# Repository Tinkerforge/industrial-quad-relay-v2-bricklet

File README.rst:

Industrial Quad Relay Bricklet 2.0
==================================

This repository contains the firmware source code and the hardware design
files. The documentation generator configs can be found at
https://github.com/Tinkerforge/generators

Repository Content
------------------

software/:
 * examples/: Examples for all supported languages
 * build/: Compiled files
 * src/: Source code of firmware
 * Makefile: Makefile to build project

hardware/:
 * Contains KiCad project files and additionally schematics as PDF

datasheets/:
 * Contains datasheets for sensors and complex ICs that are used

Hardware
--------

The hardware is designed with the open source EDA Suite KiCad
(http://www.kicad.org). Before you are able to open the files,
you have to install the Tinkerforge kicad-libraries
(https://github.com/Tinkerforge/kicad-libraries). You can either clone
them directly in hardware/ or clone them in a separate folder and
symlink them into hardware/
(ln -s kicad_path/kicad-libraries project_path/hardware). After that you
can open the .pro file in hardware/ with KiCad and from there view and
modify the schematics and the PCB layout.

Software
--------

If you want to do your own Brick/Bricklet firmware development we highly
recommend that you use our build environment setup script and read the
tutorial (https://www.tinkerforge.com/en/doc/Tutorials/Tutorial_Build_Environment/Tutorial.html).

To compile the C code we recommend you to install the newest GNU Arm Embedded
Toolchain (https://launchpad.net/gcc-arm-embedded/+download).
You also need to install bricklib2 (https://github.com/Tinkerforge/bricklib2).

You can either clone it directly in software/src/ or clone it in a
separate folder and symlink it into software/src/
(ln -s bricklib_path/bricklib2 project_path/software/src/). Finally make sure to
have CMake installed (http://www.cmake.org/cmake/resources/software.html).

After that you can build the firmware by invoking make in software/.
The firmware (.zbin) can then be found in software/build/ and uploaded
with brickv (click button "Flashing" on start screen).

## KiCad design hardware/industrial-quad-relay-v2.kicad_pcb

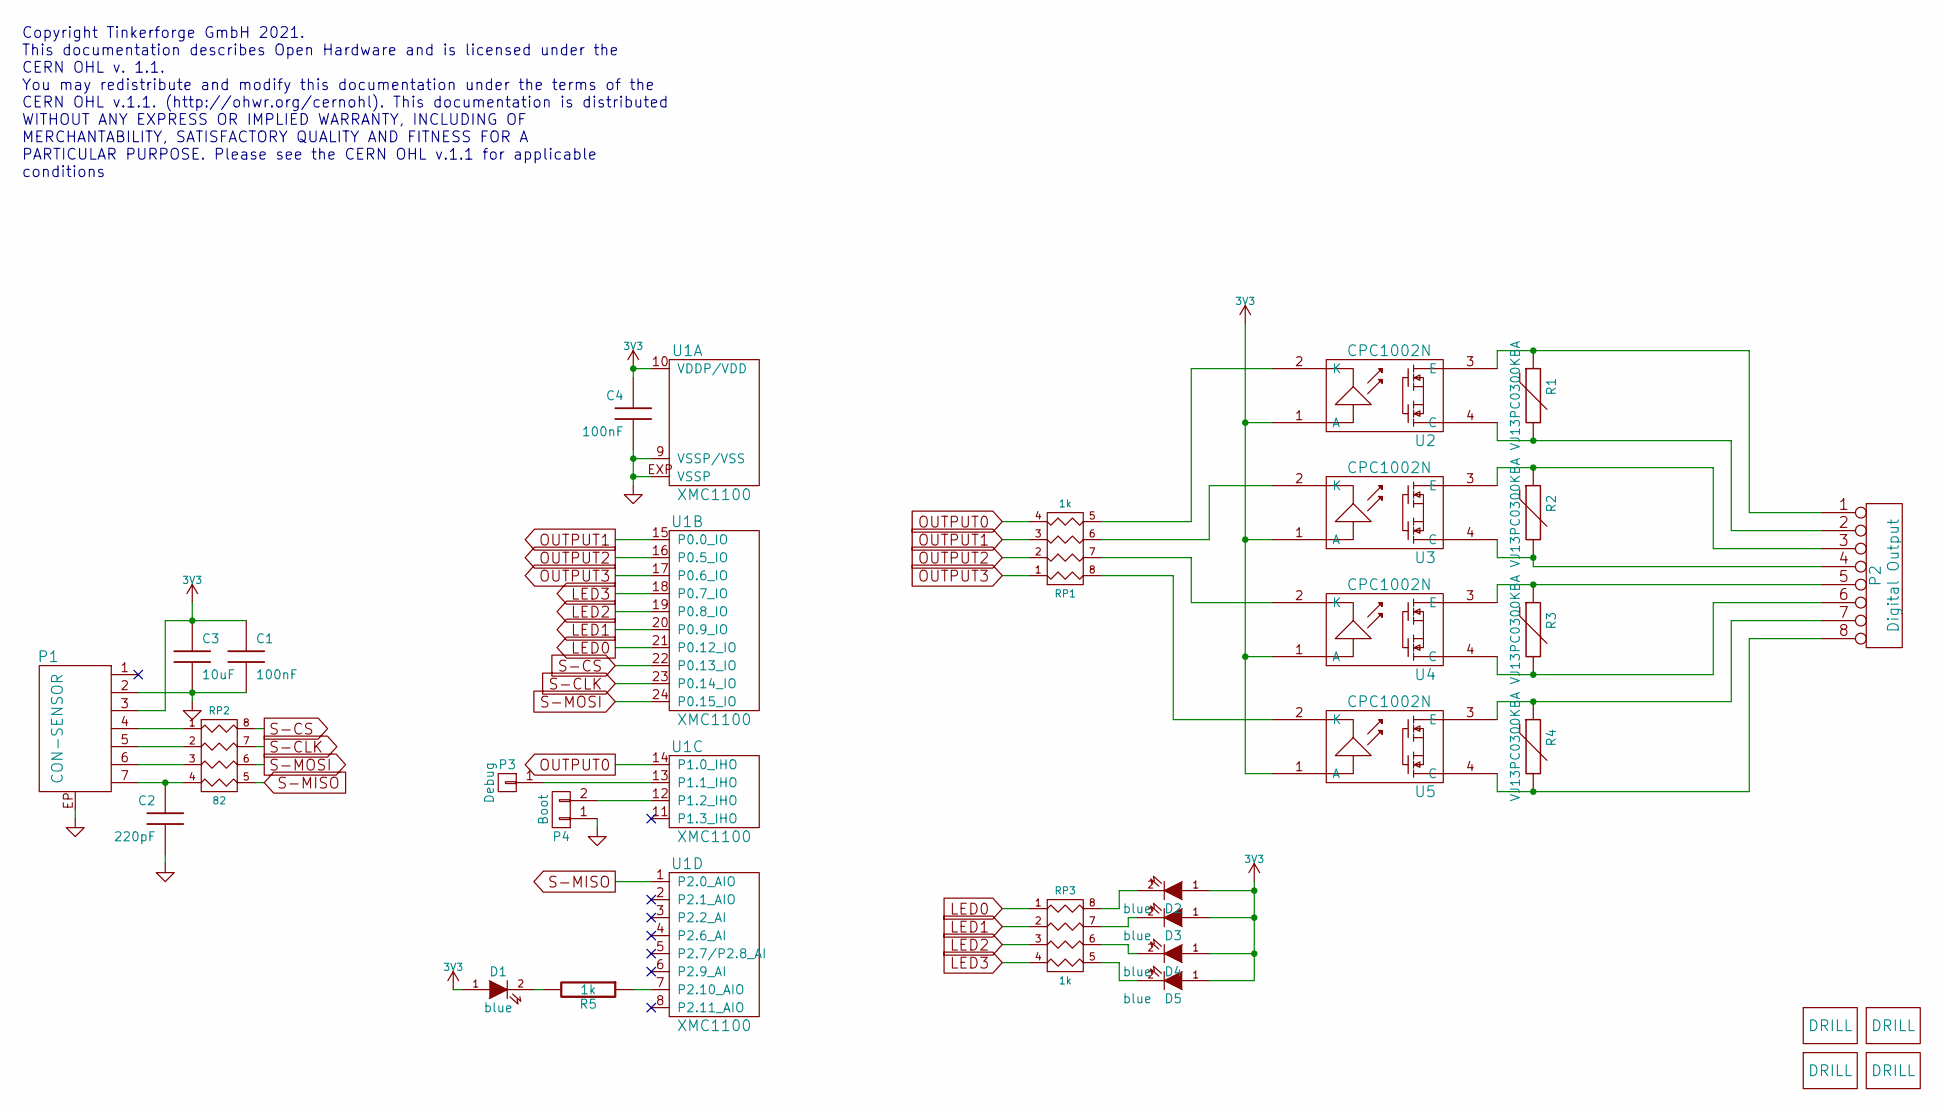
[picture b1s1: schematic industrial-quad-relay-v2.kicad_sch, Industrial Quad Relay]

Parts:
C1, C4: 100nF; C0603F
C2: 220pF; C0402F
C3: 10uF; C0805
D1, D2, D3, D4, D5: blue; D0603F
P1: CON-SENSOR; CON-SENSOR2
P2: Digital Output; OQ_8P
P3: Debug; DEBUG_PAD
P4: Boot; SolderJumper
R1, R2, R3, R4: VJ13PC0300KBA; R1210
R5: 1k; R0603F
RP1, RP3: 1k; 0603X4
RP2: 82; 4X0402
U1: XMC1100; QFN24-4x4mm-0.5mm
U2, U3, U4, U5: CPC1002N; SOP4-WIDE
U6, U7, U8, U9: DRILL; DRILL_NP

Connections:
3V3: C1.1, C3.1, C4.1, D1.1 (A), D2.1 (A), D3.1 (A), D4.1 (A), D5.1 (A), P1.3, U1.10 (VDDP/VDD), U2.1 (A), U3.1 (A), U4.1 (A), U5.1 (A)
GND: C1.2, C2.2, C3.2, C4.2, P1.2, P1.EP, P4.1, U1.9 (VSSP/VSS), U1.EXP (VSSP)
LED0: RP3.1, U1.21 (P0.12_IO)
LED1: RP3.2, U1.20 (P0.9_IO)
LED2: RP3.3, U1.19 (P0.8_IO)
LED3: RP3.4, U1.18 (P0.7_IO)
unnamed: C2.1, P1.7, RP2.4
unnamed: D1.2 (K), R5.2
unnamed: D2.2 (K), RP3.8 (R1)
unnamed: D3.2 (K), RP3.7 (R2)
unnamed: D4.2 (K), RP3.6 (R3)
unnamed: D5.2 (K), RP3.5 (R4)
unnamed: P1.4, RP2.1
unnamed: P1.5, RP2.2
unnamed: P1.6, RP2.3
unnamed: P2.1, R1.1, U2.3 (E)
unnamed: P2.2, R1.2, U2.4 (C)
unnamed: P2.3, R2.1, U3.3 (E)
unnamed: P2.4, R2.2, U3.4 (C)
unnamed: P2.5, R3.1, U4.3 (E)
unnamed: P2.6, R3.2, U4.4 (C)
unnamed: P2.7, R4.1, U5.3 (E)
unnamed: P2.8, R4.2, U5.4 (C)
unnamed: P3.1, U1.13 (P1.1_IHO)
unnamed: P4.2, U1.12 (P1.2_IHO)
unnamed: R5.1, U1.7 (P2.10_AIO)
unnamed: RP1.5 (R4), U2.2 (K)
unnamed: RP1.6 (R3), U3.2 (K)
unnamed: RP1.7 (R2), U4.2 (K)
unnamed: RP1.8 (R1), U5.2 (K)
OUTPUT0: RP1.4, U1.14 (P1.0_IHO)
OUTPUT1: RP1.3, U1.15 (P0.0_IO)
OUTPUT2: RP1.2, U1.16 (P0.5_IO)
OUTPUT3: RP1.1, U1.17 (P0.6_IO)
S-CLK: RP2.7 (R2), U1.23 (P0.14_IO)
S-CS: RP2.8 (R1), U1.22 (P0.13_IO)
S-MISO: RP2.5 (R4), U1.1 (P2.0_AIO)
S-MOSI: RP2.6 (R3), U1.24 (P0.15_IO)

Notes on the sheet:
Copyright Tinkerforge GmbH 2021. This documentation describes Open Hardware and is licensed under the CERN OHL v. 1.1. You may redistribute and modify this documentation under the terms of the CERN OHL v.1.1. (http://ohwr.org/cernohl). This documentation is distributed WITHOUT ANY EXPRESS OR IMPLIE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

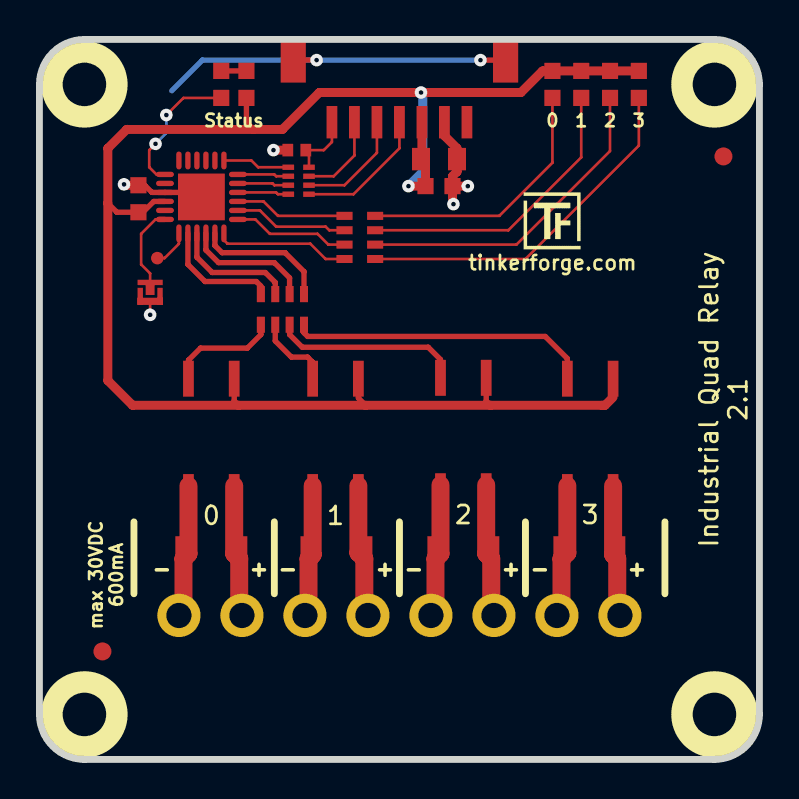
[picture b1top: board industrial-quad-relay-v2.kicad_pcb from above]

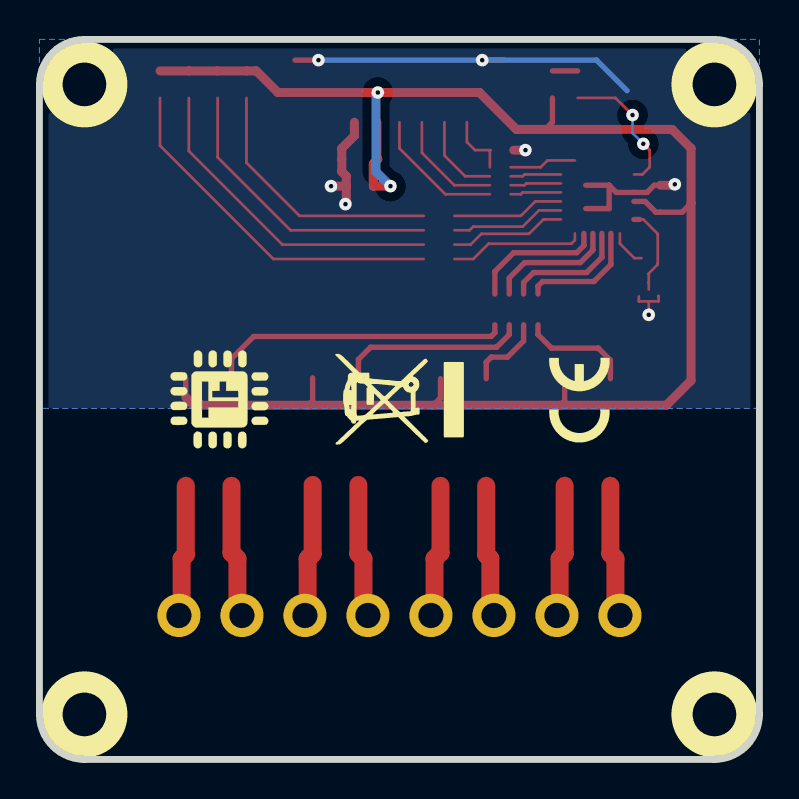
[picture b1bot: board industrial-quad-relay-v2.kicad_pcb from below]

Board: 2 copper layers, 40.0 x 40.0 mm, 34 parts (2 on the bottom side), 38 nets.

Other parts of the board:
Fiducial_Mark: VAL**; Fiducial_Mark
Fiducial_Mark#2: VAL**; Fiducial_Mark
VAL: WEEE_7mm
VAL#2: CE_5mm

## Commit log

2018-01-12 add readme file
2018-01-12 new hardware prototype
2018-01-12 fix headers
2018-02-08 Add software for Industrial Quad Relay Bricklet 2.0
2018-02-20 Cleanup KiCad libraries config
    Ensure LibDir=kicad-libraries and LibName1=tinkerforge.
    Remove special library.
2018-03-05 Remove unused flash-size define
2018-03-15 add four status led, routing optimized
2018-03-15 fix logo positions
2018-03-16 change product name placement
2018-03-27 Rename "pin" to "channel"
2018-03-27 specify processor
2018-04-11 Add info LED config support
2018-04-16 Add 3d model (*.FCStd & *.step)
2018-04-30 Fix pin definitions
2018-05-02 Rename info LED to channel LED
2018-05-04 Rename files
2018-05-04 Add schematic PDF
2018-05-04 configuration adapted to new led routing
2018-05-29 Simplify output-value name to just value
2018-05-29 Implement bool (un)packing
2018-06-04 Disable debug
2018-06-07 Update changelog for initial release
2018-06-18 Change capacitor footprint(s) to C0402F
2018-06-28 Fix readme
2018-07-11 Add Makefile with docker support
2018-07-11 Remove obsolete generate_makefile scripts
2018-07-11 Update directory structure and build instructions
2018-07-18 Add examples
2018-10-04 Increase version for new release (changes in bricklib2)
2018-10-04 Add rev to changelog
2018-11-06 Add rust examples
2018-11-07 rust: Accept host names for ip connection, fix naming inconsistencies
2018-12-14 Add go examples.
2018-12-18 go: Change import path.
2018-12-18 go: Change import path again.
2018-12-20 rust: Reformat examples.
2019-01-24 mqtt: Add examples.
2019-01-24 mqtt: Fix example header.
2019-01-24 mqtt: Remove executable bit in example permissions.
2019-01-24 go: Minor example fixes.
2019-01-24 mqtt: Minor example fixes.
2019-01-29 rust: Fix unused loop index.
2019-03-28 c: Examples: Pre-declare array used as parameter.
2019-05-02 Fix off-by-one in channel parameter range check
2019-05-07 Make monoflop time-remaining count down instead of up
    Don't use cached monoflop state, but always operate on the current state.
2020-01-13 examples: Use python3 input instead of python2 raw_input.
2020-01-13 examples: mqtt: Remove trailing whitespace.
2020-03-16 Whitespace
2020-03-23 mqtt: Update for loop style
2020-04-07 examples: rust: Always block when calling bindings functions.
2020-08-19 Add uc examples.
2020-08-25 uc: Fix whitespace
2020-08-27 uc: Fix warnings.
2020-09-02 uc: Add example driver note.
2021-10-25 Update KiCad link
    https://www.kicad.org/blog/2021/10/Avoid-links-to-former-kicad-domain/
2021-12-03 add version 2.1
    change CPC1020N -> CPC1002N
2021-12-13 add silkscreen polarity markings
2022-04-13 update schematic
2022-04-13 add datasheet
2022-04-19 examples: uc: Rename TF_HalContext to TF_HAL.
2022-04-27 uc: Adapt to bindings changes
2022-07-06 Add license files.
2023-06-20 move to new kicad version
2025-10-04 Fix compatibility with new Docker build image (GCC 14.2.1)

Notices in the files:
hardware/industrial-quad-relay-v2.kicad_pcb:
Licensed under CERN OHL v.1.1
Copyright (©) 2021, B.Nordmeyer
